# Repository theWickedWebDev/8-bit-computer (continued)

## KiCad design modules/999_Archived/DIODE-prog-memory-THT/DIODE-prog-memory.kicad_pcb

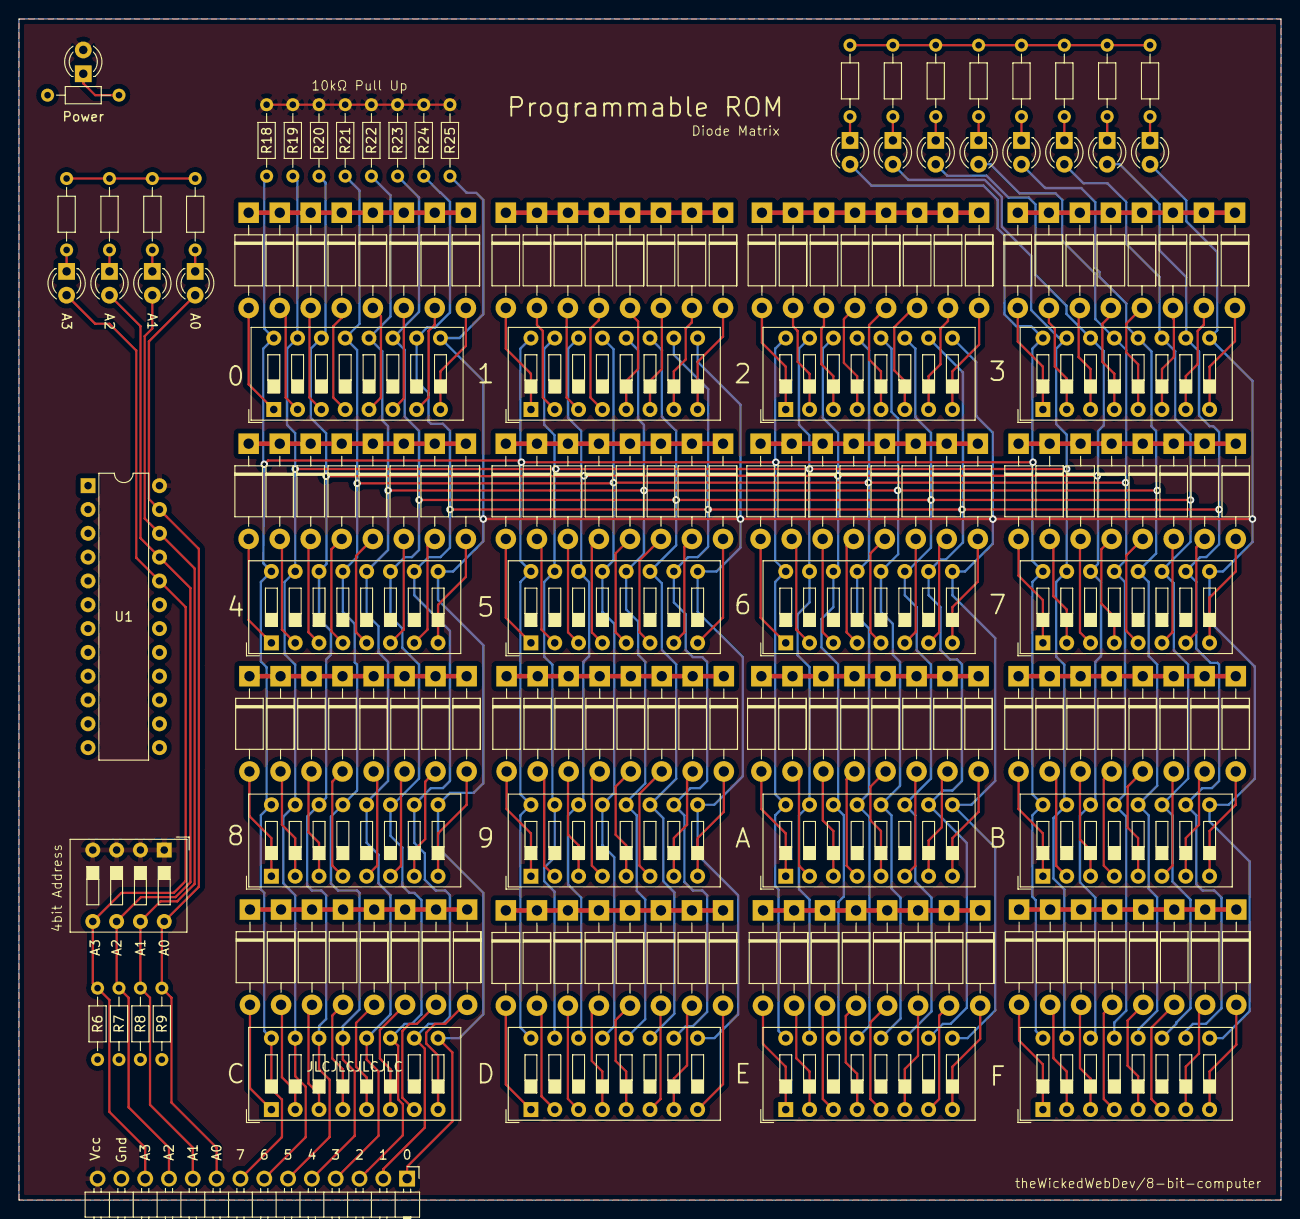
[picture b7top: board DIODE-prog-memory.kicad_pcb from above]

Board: 2 copper layers, 134.6 x 126.0 mm, 73 parts (0 on the bottom side), 171 nets.

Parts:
D1, D2, D3, D4, D5, D6, D7, D8, D9, D10, D11, D12, D13: LED; LED_D3.0mm
J1: Conn_01x14; PinHeader_1x14_P2.54mm_Horizontal
J4, J5, J6, J7, J8, J9, J10, J11, J12, J13, J14, J15, J16, J17, J18, J19: Conn_02x08_Odd_Even; Diode_Array_1x08
R1, R2, R3, R4, R5, R6, R7, R8, R9, R10, R11, R12, R13, R14, R15, R16, R17, R18, R19, R20, R21, R22, R23, R24, R25: R_US; R_Axial_DIN0204_L3.6mm_D1.6mm_P7.62mm_Horizontal
SW1: SW_DIP_x04; SW_DIP_SPSTx04_Slide_9.78x12.34mm_W7.62mm_P2.54mm
SW2, SW3, SW4, SW5, SW6, SW7, SW8, SW9, SW10, SW11, SW12, SW13, SW14, SW15, SW16, SW17: SW_DIP_x08; SW_DIP_SPSTx08_Slide_9.78x22.5mm_W7.62mm_P2.54mm
U1: 74HC154D,653; DIP-24_W7.62mm

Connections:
A: D13.2, J1.8, R18.2, SW2.16, SW3.16, SW4.16, SW5.16, SW6.16, SW7.16, SW8.16, SW9.16, SW10.16, SW11.16, SW12.16, SW13.16, SW14.16, SW15.16, SW16.16, SW17.16
B: D12.2, J1.7, R19.2, SW2.15, SW3.15, SW4.15, SW5.15, SW6.15, SW7.15, SW8.15, SW9.15, SW10.15, SW11.15, SW12.15, SW13.15, SW14.15, SW15.15, SW16.15, SW17.15
C: D11.2, J1.6, R20.2, SW2.14, SW3.14, SW4.14, SW5.14, SW6.14, SW7.14, SW8.14, SW9.14, SW10.14, SW11.14, SW12.14, SW13.14, SW14.14, SW15.14, SW16.14, SW17.14
D: D10.2, J1.5, R21.2, SW2.13, SW3.13, SW4.13, SW5.13, SW6.13, SW7.13, SW8.13, SW9.13, SW10.13, SW11.13, SW12.13, SW13.13, SW14.13, SW15.13, SW16.13, SW17.13
E: D9.2, J1.4, R22.2, SW2.12, SW3.12, SW4.12, SW5.12, SW6.12, SW7.12, SW8.12, SW9.12, SW10.12, SW11.12, SW12.12, SW13.12, SW14.12, SW15.12, SW16.12, SW17.12
F: D8.2, J1.3, R23.2, SW2.11, SW3.11, SW4.11, SW5.11, SW6.11, SW7.11, SW8.11, SW9.11, SW10.11, SW11.11, SW12.11, SW13.11, SW14.11, SW15.11, SW16.11, SW17.11
G: D7.2, J1.2, R24.2, SW2.10, SW3.10, SW4.10, SW5.10, SW6.10, SW7.10, SW8.10, SW9.10, SW10.10, SW11.10, SW12.10, SW13.10, SW14.10, SW15.10, SW16.10, SW17.10
GND: J1.13, R1.2, R2.2, R3.2, R4.2, R5.2, R6.1, R7.1, R8.1, R9.1, R10.1, R11.1, R12.1, R13.1, R14.1, R15.1, R16.1, R17.1, U1.12, U1.18, U1.19
H: D6.2, J1.1, R25.2, SW2.9, SW3.9, SW4.9, SW5.9, SW6.9, SW7.9, SW8.9, SW9.9, SW10.9, SW11.9, SW12.9, SW13.9, SW14.9, SW15.9, SW16.9, SW17.9
unnamed: D1.1, R1.1
unnamed: D2.1, R2.1
unnamed: D2.2, J1.12, R6.2, SW1.5, U1.20
unnamed: D3.1, R3.1
unnamed: D3.2, J1.11, R7.2, SW1.6, U1.21
unnamed: D4.1, R4.1
unnamed: D4.2, J1.10, R8.2, SW1.7, U1.22
unnamed: D5.1, R5.1
unnamed: D5.2, J1.9, R9.2, SW1.8, U1.23
unnamed: D6.1, R10.2
unnamed: D7.1, R11.2
unnamed: D8.1, R12.2
unnamed: D9.1, R13.2
unnamed: D10.1, R14.2
unnamed: D11.1, R15.2
unnamed: D12.1, R16.2
unnamed: D13.1, R17.2
unnamed: J4.1, J4.3, J4.5, J4.7, J4.9, J4.11, J4.13, J4.15
unnamed: J4.2, SW2.1
unnamed: J4.4, SW2.2
unnamed: J4.6, SW2.3
unnamed: J4.8, SW2.4
unnamed: J4.10, SW2.5
unnamed: J4.12, SW2.6
unnamed: J4.14, SW2.7
unnamed: J4.16, SW2.8
unnamed: J5.1, J5.3, J5.5, J5.7, J5.9, J5.11, J5.13, J5.15
unnamed: J5.2, SW3.1
unnamed: J5.4, SW3.2
unnamed: J5.6, SW3.3
unnamed: J5.8, SW3.4
unnamed: J5.10, SW3.5
unnamed: J5.12, SW3.6
unnamed: J5.14, SW3.7
unnamed: J5.16, SW3.8
unnamed: J6.1, J6.3, J6.5, J6.7, J6.9, J6.11, J6.13, J6.15
unnamed: J6.2, SW11.1
unnamed: J6.4, SW11.2
unnamed: J6.6, SW11.3
unnamed: J6.8, SW11.4
unnamed: J6.10, SW11.5
unnamed: J6.12, SW11.6
unnamed: J6.14, SW11.7
unnamed: J6.16, SW11.8
unnamed: J7.1, J7.3, J7.5, J7.7, J7.9, J7.11, J7.13, J7.15
unnamed: J7.2, SW10.1
unnamed: J7.4, SW10.2
unnamed: J7.6, SW10.3
unnamed: J7.8, SW10.4
unnamed: J7.10, SW10.5
unnamed: J7.12, SW10.6
unnamed: J7.14, SW10.7
unnamed: J7.16, SW10.8
unnamed: J8.1, J8.3, J8.5, J8.7, J8.9, J8.11, J8.13, J8.15
unnamed: J8.2, SW5.1
unnamed: J8.4, SW5.2
unnamed: J8.6, SW5.3
unnamed: J8.8, SW5.4
unnamed: J8.10, SW5.5
unnamed: J8.12, SW5.6
unnamed: J8.14, SW5.7
unnamed: J8.16, SW5.8
unnamed: J9.1, J9.3, J9.5, J9.7, J9.9, J9.11, J9.13, J9.15
unnamed: J9.2, SW4.1
unnamed: J9.4, SW4.2
unnamed: J9.6, SW4.3
unnamed: J9.8, SW4.4
unnamed: J9.10, SW4.5
unnamed: J9.12, SW4.6
unnamed: J9.14, SW4.7
unnamed: J9.16, SW4.8
unnamed: J10.1, J10.3, J10.5, J10.7, J10.9, J10.11, J10.13, J10.15
unnamed: J10.2, SW13.1
unnamed: J10.4, SW13.2
unnamed: J10.6, SW13.3
unnamed: J10.8, SW13.4
unnamed: J10.10, SW13.5
unnamed: J10.12, SW13.6
unnamed: J10.14, SW13.7
unnamed: J10.16, SW13.8
unnamed: J11.1, J11.3, J11.5, J11.7, J11.9, J11.11, J11.13, J11.15
unnamed: J11.2, SW12.1
unnamed: J11.4, SW12.2
unnamed: J11.6, SW12.3
unnamed: J11.8, SW12.4
unnamed: J11.10, SW12.5
unnamed: J11.12, SW12.6
unnamed: J11.14, SW12.7
unnamed: J11.16, SW12.8
unnamed: J12.1, J12.3, J12.5, J12.7, J12.9, J12.11, J12.13, J12.15
unnamed: J12.2, SW7.1
unnamed: J12.4, SW7.2
unnamed: J12.6, SW7.3
unnamed: J12.8, SW7.4
unnamed: J12.10, SW7.5
unnamed: J12.12, SW7.6
unnamed: J12.14, SW7.7
unnamed: J12.16, SW7.8
unnamed: J13.1, J13.3, J13.5, J13.7, J13.9, J13.11, J13.13, J13.15
unnamed: J13.2, SW6.1
unnamed: J13.4, SW6.2
unnamed: J13.6, SW6.3
unnamed: J13.8, SW6.4
unnamed: J13.10, SW6.5
unnamed: J13.12, SW6.6
unnamed: J13.14, SW6.7
unnamed: J13.16, SW6.8
unnamed: J14.1, J14.3, J14.5, J14.7, J14.9, J14.11, J14.13, J14.15
unnamed: J14.2, SW16.1
unnamed: J14.4, SW16.2
unnamed: J14.6, SW16.3
unnamed: J14.8, SW16.4
unnamed: J14.10, SW16.5
unnamed: J14.12, SW16.6
unnamed: J14.14, SW16.7
unnamed: J14.16, SW16.8
unnamed: J15.1, J15.3, J15.5, J15.7, J15.9, J15.11, J15.13, J15.15
unnamed: J15.2, SW14.1
unnamed: J15.4, SW14.2
unnamed: J15.6, SW14.3
unnamed: J15.8, SW14.4
unnamed: J15.10, SW14.5
unnamed: J15.12, SW14.6
unnamed: J15.14, SW14.7
unnamed: J15.16, SW14.8
unnamed: J16.1, J16.3, J16.5, J16.7, J16.9, J16.11, J16.13, J16.15
unnamed: J16.2, SW9.1
unnamed: J16.4, SW9.2
unnamed: J16.6, SW9.3
unnamed: J16.8, SW9.4
unnamed: J16.10, SW9.5
unnamed: J16.12, SW9.6
unnamed: J16.14, SW9.7
unnamed: J16.16, SW9.8
unnamed: J17.1, J17.3, J17.5, J17.7, J17.9, J17.11, J17.13, J17.15
unnamed: J17.2, SW8.1
unnamed: J17.4, SW8.2
unnamed: J17.6, SW8.3
unnamed: J17.8, SW8.4
unnamed: J17.10, SW8.5
unnamed: J17.12, SW8.6
unnamed: J17.14, SW8.7
unnamed: J17.16, SW8.8
unnamed: J18.1, J18.3, J18.5, J18.7, J18.9, J18.11, J18.13, J18.15
unnamed: J18.2, SW17.1
unnamed: J18.4, SW17.2
unnamed: J18.6, SW17.3
unnamed: J18.8, SW17.4
unnamed: J18.10, SW17.5
unnamed: J18.12, SW17.6
unnamed: J18.14, SW17.7
unnamed: J18.16, SW17.8
unnamed: J19.1, J19.3, J19.5, J19.7, J19.9, J19.11, J19.13, J19.15
unnamed: J19.2, SW15.1
unnamed: J19.4, SW15.2
unnamed: J19.6, SW15.3
unnamed: J19.8, SW15.4
unnamed: J19.10, SW15.5
unnamed: J19.12, SW15.6
unnamed: J19.14, SW15.7
unnamed: J19.16, SW15.8
VCC: D1.2, J1.14, R18.1, R19.1, R20.1, R21.1, R22.1, R23.1, R24.1, R25.1, SW1.1, SW1.2, SW1.3, SW1.4, U1.24
